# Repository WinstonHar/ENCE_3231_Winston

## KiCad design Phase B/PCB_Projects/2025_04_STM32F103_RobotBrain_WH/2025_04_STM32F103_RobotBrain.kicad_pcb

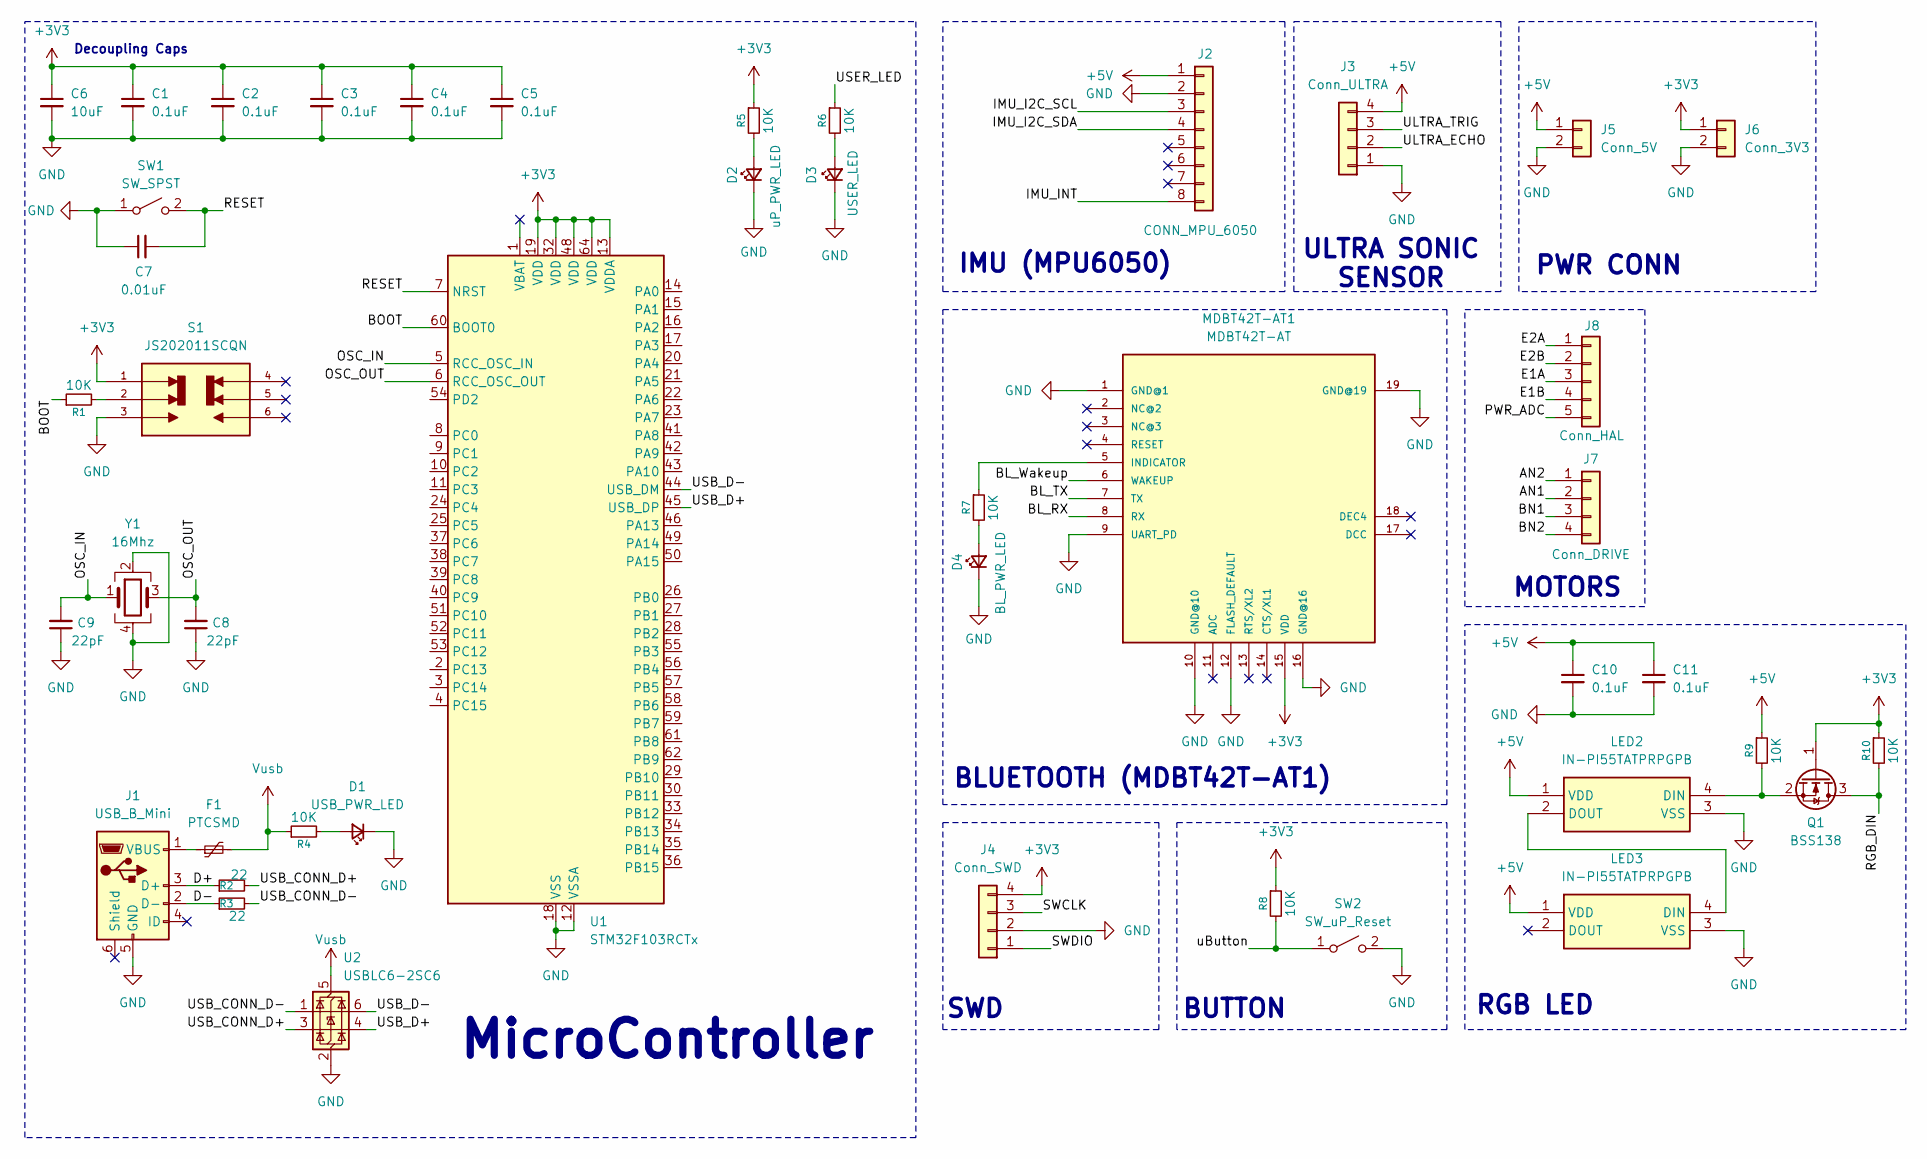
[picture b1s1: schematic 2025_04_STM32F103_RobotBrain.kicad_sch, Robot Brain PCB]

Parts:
C1, C2, C3, C4, C5, C10, C11: 0.1uF; C_0805_2012Metric_Pad1.18x1.45mm_HandSolder; Mfr #P KAM21BR71H104JT
C6: 10uF; C_0805_2012Metric_Pad1.18x1.45mm_HandSolder; Mfr #P LMK212ABJ106KG-T
C7: 0.01uF; C_0805_2012Metric_Pad1.18x1.45mm_HandSolder; Mfr #P KAF21BR72A103JT
C8, C9: 22pF; C_0805_2012Metric_Pad1.18x1.45mm_HandSolder; Mfr #P 0805ZA220JAT2A
D1: USB_PWR_LED; LED_0805_2012Metric_Pad1.15x1.40mm_HandSolder
D2: uP_PWR_LED; LED_0805_2012Metric_Pad1.15x1.40mm_HandSolder
D3: USER_LED; LED_0805_2012Metric_Pad1.15x1.40mm_HandSolder
D4: BL_PWR_LED; LED_0805_2012Metric_Pad1.15x1.40mm_HandSolder
F1: PTCSMD; Fuse_0805_2012Metric_Pad1.15x1.40mm_HandSolder; Mfr #P 0ZCK0050AF2E
J1: USB_B_Mini; USB_Mini-B_Lumberg_2486_01_Horizontal
J2: CONN_MPU_6050; PinSocket_1x08_P2.54mm_Vertical
J3: Conn_ULTRA; PinSocket_1x04_P2.54mm_Vertical
J4: Conn_SWD; PinSocket_1x04_P2.54mm_Vertical
J5: Conn_5V; JST_XH_B2B-XH-A_1x02_P2.50mm_Vertical
J6: Conn_3V3; JST_XH_B2B-XH-A_1x02_P2.50mm_Vertical
J7: Conn_DRIVE; JST_XH_B4B-XH-A_1x04_P2.50mm_Vertical
J8: Conn_HAL; JST_XH_B5B-XH-A_1x05_P2.50mm_Vertical
LED2, LED3: IN-PI55TATPRPGPB; INPI55TATPRPGPB; Manufacturer_Part_Number IN-PI55TATPRPGPB; Mouser Part Number 743-IN-PI55TATPRPGPB
MDBT42T-AT1: MDBT42T-AT; MDBT42T
Q1: BSS138; SOT-23; Mfr #P BSS138
R1, R4, R5, R6, R7, R8, R9, R10: 10K; R_0805_2012Metric_Pad1.20x1.40mm_HandSolder; Mfr #P RK73B2ATTE103J
R2, R3: 22; R_0805_2012Metric_Pad1.20x1.40mm_HandSolder; Mfr #P RC0805FR-7W22RL
S1: JS202011SCQN; SW_JS202011SCQN; PARTREV 26 May 22
SW1: SW_SPST; SW_uP_Reset
SW2: SW_uP_Reset; SW_SPST_PTS647_Sx50
U1: STM32F103RCTx; LQFP-64_10x10mm_P0.5mm; Mfr #P STM32F103RCT6
U2: USBLC6-2SC6; SOT-23-6
Y1: 16Mhz; Crystal_SMD_Abracon_ABM8G-4Pin_3.2x2.5mm; Mfg #p ABM8G-16.000MHZ-18-D2Y-T3

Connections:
+3V3: C1.1, C2.1, C3.1, C4.1, C5.1, C6.1, J4.4, J6.1, MDBT42T-AT1.15 (VDD), Q1.1 (G), R5.1, R8.1, R10.1, S1.1, U1.13 (VDDA), U1.19 (VDD), U1.32 (VDD), U1.48 (VDD), U1.64 (VDD)
+5V: C10.1, C11.1, J2.1, J3.4, J5.1, LED2.1 (VDD), LED3.1 (VDD), R9.1
/AN1: J7.2
/AN2: J7.1
/BL_RX: MDBT42T-AT1.8 (RX)
/BL_TX: MDBT42T-AT1.7 (TX)
/BL_Wakeup: MDBT42T-AT1.6 (WAKEUP)
/BN1: J7.3
/BN2: J7.4
/BOOT: R1.1, U1.60 (BOOT0)
/D+: J1.3 (D+), R2.1
/D-: J1.2 (D-), R3.1
/E1A: J8.3
/E1B: J8.4
/E2A: J8.1
/E2B: J8.2
/IMU_I2C_SCL: J2.3
/IMU_I2C_SDA: J2.4
/IMU_INT: J2.8
/OSC_IN: C9.2, U1.5 (RCC_OSC_IN), Y1.1
/OSC_OUT: C8.2, U1.6 (RCC_OSC_OUT), Y1.3
/PWR_ADC: J8.5
/RESET: C7.2, SW1.2 (B), U1.7 (NRST)
/RGB_DIN: Q1.3 (D), R10.2
/SWCLK: J4.3
/SWDIO: J4.1
/ULTRA_ECHO: J3.2
/ULTRA_TRIG: J3.3
/USB_CONN_D+: R2.2, U2.3 (I/O2)
/USB_CONN_D-: R3.2, U2.1 (I/O1)
/USB_D+: U1.45 (USB_DP), U2.4 (I/O2)
/USB_D-: U1.44 (USB_DM), U2.6 (I/O1)
/USER_LED: R6.1
/uButton: R8.2, SW2.1 (A)
GND: C1.2, C2.2, C3.2, C4.2, C5.2, C6.2, C7.1, C8.1, C9.1, C10.2, C11.2, D1.1 (K), D2.1 (K), D3.1 (K), D4.1 (K), J1.5 (GND), J2.2, J3.1, J4.2, J5.2, J6.2, LED2.3 (VSS), LED3.3 (VSS), MDBT42T-AT1.1 (GND@1), MDBT42T-AT1.9 (UART_PD), MDBT42T-AT1.10 (GND@10), MDBT42T-AT1.12 (FLASH_DEFAULT), MDBT42T-AT1.16 (GND@16), MDBT42T-AT1.19 (GND@19), S1.3, SW1.1 (A), SW2.2 (B), U1.12 (VSSA), U1.18 (VSS), U1.31 (VSS), U1.47 (VSS), U1.63 (VSS), U2.2 (GND), Y1.2, Y1.4
unnamed: D1.2 (A), R4.2
unnamed: D2.2 (A), R5.2
unnamed: D3.2 (A), R6.2
unnamed: D4.2 (A), R7.2
unnamed: F1.1, J1.1 (VBUS)
unnamed: LED2.4 (DIN), Q1.2 (S), R9.2
unnamed: LED2.2 (DOUT), LED3.4 (DIN)
unnamed: MDBT42T-AT1.5 (INDICATOR), R7.1
unnamed: R1.2, S1.2
Vusb: F1.2, R4.1, U2.5 (VBUS)

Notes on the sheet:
BLUETOOTH (MDBT42T-AT1)
ULTRA SONIC SENSOR
RGB LED
PWR CONN
BUTTON
MOTORS
IMU (MPU6050)
MicroController
Decoupling Caps
SWD

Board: 2 copper layers, 42 parts (0 on the bottom side), 25 nets, no tracks yet.

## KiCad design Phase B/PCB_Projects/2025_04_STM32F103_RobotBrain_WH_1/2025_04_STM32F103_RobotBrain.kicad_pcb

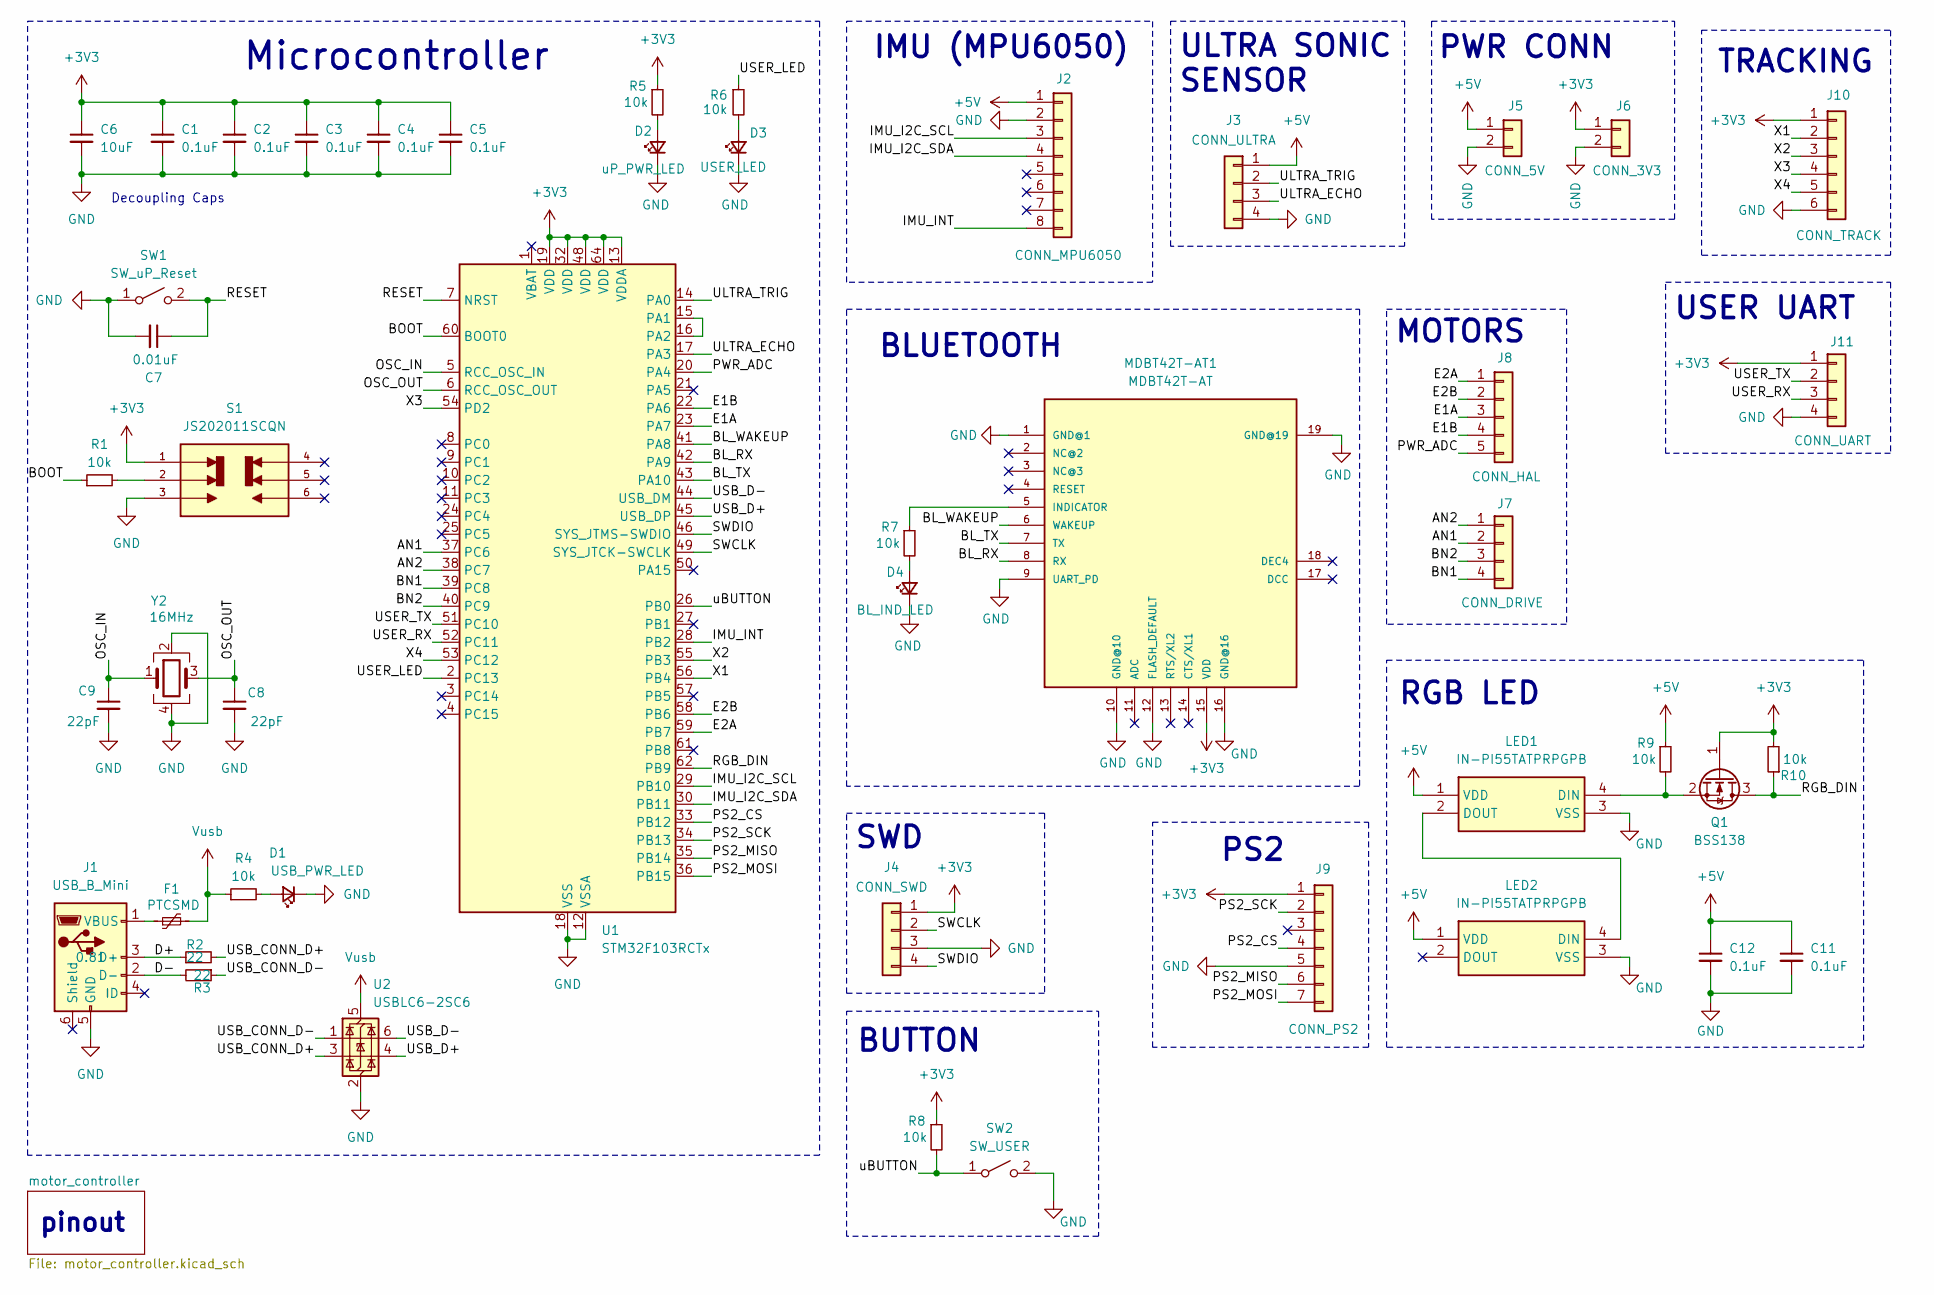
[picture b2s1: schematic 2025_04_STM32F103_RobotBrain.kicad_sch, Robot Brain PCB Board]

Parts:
C1, C2, C3, C4, C5, C11, C12: 0.1uF; C_0805_2012Metric_Pad1.18x1.45mm_HandSolder; Mfr #P KAM21BR71H104JT
C6: 10uF; C_0805_2012Metric_Pad1.18x1.45mm_HandSolder; Mfr #P LMK212ABJ106KG-T
C7: 0.01uF; C_0805_2012Metric_Pad1.18x1.45mm_HandSolder; Mfr #P KAF21BR72A103JT
C8, C9: 22pF; C_0805_2012Metric_Pad1.18x1.45mm_HandSolder; Mfr #P 0805ZA220JAT2A
D1: USB_PWR_LED; LED_0805_2012Metric_Pad1.15x1.40mm_HandSolder; Mfr #P 150080VS75000
D2: uP_PWR_LED; LED_0805_2012Metric_Pad1.15x1.40mm_HandSolder; Mfr #P 150080VS75000
D3: USER_LED; LED_0805_2012Metric_Pad1.15x1.40mm_HandSolder; Mfr #P 150080RS75000
D4: BL_IND_LED; LED_0805_2012Metric_Pad1.15x1.40mm_HandSolder; Mfr #P 150080VS75000
F1: PTCSMD; Fuse_0805_2012Metric_Pad1.15x1.40mm_HandSolder; Mfr #P 0ZCK0050AF2E
J1: USB_B_Mini; USB_Mini-B_Lumberg_2486_01_Horizontal; Mfr #P UJ2-MBH-4-SMT-TR
J2: CONN_MPU6050; PinSocket_1x08_P2.54mm_Vertical
J3: CONN_ULTRA; PinSocket_1x04_P2.54mm_Vertical
J4: CONN_SWD; PinSocket_1x04_P2.54mm_Vertical
J5: CONN_5V; JST_XH_B2B-XH-A_1x02_P2.50mm_Vertical
J6: CONN_3V3; JST_XH_B2B-XH-A_1x02_P2.50mm_Vertical
J7: CONN_DRIVE; JST_XH_B4B-XH-A_1x04_P2.50mm_Vertical
J8: CONN_HAL; JST_XH_B5B-XH-A_1x05_P2.50mm_Vertical
J9: CONN_PS2; PinHeader_1x07_P2.54mm_Vertical
J10: CONN_TRACK; JST_XH_B6B-XH-A_1x06_P2.50mm_Vertical
J11: CONN_UART; JST_XH_B4B-XH-A_1x04_P2.50mm_Vertical
LED1, LED2: IN-PI55TATPRPGPB; INPI55TATPRPGPB; Manufacturer_Part_Number IN-PI55TATPRPGPB; Mouser Part Number 743-IN-PI55TATPRPGPB
MDBT42T-AT1: MDBT42T-AT; MDBT42T
Q1: BSS138; SOT-23; Mfr #P BSS138
R1, R4, R5, R6, R7, R8, R9, R10: 10k; R_0805_2012Metric_Pad1.20x1.40mm_HandSolder; Mfr #P RK73B2ATTE103J
R2, R3: 22; R_0805_2012Metric_Pad1.20x1.40mm_HandSolder; Mfr #P RC0805FR-7W22RL
S1: JS202011SCQN; SW_uP_Boot; PARTREV 26 May 22
SW1: SW_uP_Reset; Mfr #P 434121025816
SW2: SW_USER; SW_SPST_PTS647_Sx50; Mfr #P TL3305BF100QG
U1: STM32F103RCTx; LQFP-64_10x10mm_P0.5mm; Mfr #P STM32F103RCT6
U2: USBLC6-2SC6; SOT-23-6; Mfr #P USBLC6-2SC6
Y2: 16MHz; Crystal_SMD_Abracon_ABM8G-4Pin_3.2x2.5mm; Mfr #P ABM8-16.000MHZ-D1X-T

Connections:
+3V3: C1.1, C2.1, C3.1, C4.1, C5.1, C6.1, J4.1, J6.1, J9.1, J10.1, J11.1, MDBT42T-AT1.15 (VDD), Q1.1 (G), R5.1, R8.1, R10.2, S1.1, U1.13 (VDDA), U1.19 (VDD), U1.32 (VDD), U1.48 (VDD), U1.64 (VDD)
+5V: C11.1, C12.1, J2.1, J3.1, J5.1, LED1.1 (VDD), LED2.1 (VDD), R9.1
/AN1: J7.2, U1.37 (PC6)
/AN2: J7.1, U1.38 (PC7)
/BL_RX: MDBT42T-AT1.8 (RX), U1.42 (PA9)
/BL_TX: MDBT42T-AT1.7 (TX), U1.43 (PA10)
/BL_WAKEUP: MDBT42T-AT1.6 (WAKEUP), U1.41 (PA8)
/BN1: J7.4, U1.39 (PC8)
/BN2: J7.3, U1.40 (PC9)
/BOOT: R1.1, U1.60 (BOOT0)
/D+: J1.3 (D+), R2.1
/D-: J1.2 (D-), R3.2
/E1A: J8.3, U1.23 (PA7)
/E1B: J8.4, U1.22 (PA6)
/E2A: J8.1, U1.59 (PB7)
/E2B: J8.2, U1.58 (PB6)
/IMU_I2C_SCL: J2.3, U1.29 (PB10)
/IMU_I2C_SDA: J2.4, U1.30 (PB11)
/IMU_INT: J2.8, U1.28 (PB2)
/OSC_IN: C9.1, U1.5 (RCC_OSC_IN), Y2.1
/OSC_OUT: C8.1, U1.6 (RCC_OSC_OUT), Y2.3
/PS2_CS: J9.4, U1.33 (PB12)
/PS2_MISO: J9.6, U1.35 (PB14)
/PS2_MOSI: J9.7, U1.36 (PB15)
/PS2_SCK: J9.2, U1.34 (PB13)
/PWR_ADC: J8.5, U1.20 (PA4)
/RESET: C7.1, SW1.2 (B), U1.7 (NRST)
/RGB_DIN: Q1.3 (D), R10.1, U1.62 (PB9)
/SWCLK: J4.2, U1.49 (SYS_JTCK-SWCLK)
/SWDIO: J4.4, U1.46 (SYS_JTMS-SWDIO)
/ULTRA_ECHO: J3.3, U1.17 (PA3)
/ULTRA_TRIG: J3.2, U1.14 (PA0)
/USB_CONN_D+: R2.2, U2.3 (I/O2)
/USB_CONN_D-: R3.1, U2.1 (I/O1)
/USB_D+: U1.45 (USB_DP), U2.4 (I/O2)
/USB_D-: U1.44 (USB_DM), U2.6 (I/O1)
/USER_LED: R6.1, U1.2 (PC13)
/USER_RX: J11.3, U1.52 (PC11)
/USER_TX: J11.2, U1.51 (PC10)
/X1: J10.2, U1.56 (PB4)
/X2: J10.3, U1.55 (PB3)
/X3: J10.4, U1.54 (PD2)
/X4: J10.5, U1.53 (PC12)
/uBUTTON: R8.2, SW2.1 (A), U1.26 (PB0)
GND: C1.2, C2.2, C3.2, C4.2, C5.2, C6.2, C7.2, C8.2, C9.2, C11.2, C12.2, D1.1 (K), D2.1 (K), D3.1 (K), D4.1 (K), J1.5 (GND), J2.2, J3.4, J4.3, J5.2, J6.2, J9.5, J10.6, J11.4, LED1.3 (VSS), LED2.3 (VSS), MDBT42T-AT1.1 (GND@1), MDBT42T-AT1.9 (UART_PD), MDBT42T-AT1.10 (GND@10), MDBT42T-AT1.12 (FLASH_DEFAULT), MDBT42T-AT1.16 (GND@16), MDBT42T-AT1.19 (GND@19), S1.3, SW1.1 (A), SW2.2 (B), U1.12 (VSSA), U1.18 (VSS), U1.31 (VSS), U1.47 (VSS), U1.63 (VSS), U2.2 (GND), Y2.2, Y2.4
unnamed: D1.2 (A), R4.2
unnamed: D2.2 (A), R5.2
unnamed: D3.2 (A), R6.2
unnamed: D4.2 (A), R7.2
unnamed: F1.1, J1.1 (VBUS)
unnamed: LED1.4 (DIN), Q1.2 (S), R9.2
unnamed: LED1.2 (DOUT), LED2.4 (DIN)
unnamed: MDBT42T-AT1.5 (INDICATOR), R7.1
unnamed: R1.2, S1.2
unnamed: U1.15 (PA1), U1.16 (PA2)
Vusb: F1.2, R4.1, U2.5 (VBUS)

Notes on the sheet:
PWR CONN
ULTRA SONIC SENSOR
Decoupling Caps
BUTTON
MOTORS
PS2
RGB LED
Microcontroller
TRACKING
pinout
IMU (MPU6050)
SWD
USER UART
BLUETOOTH

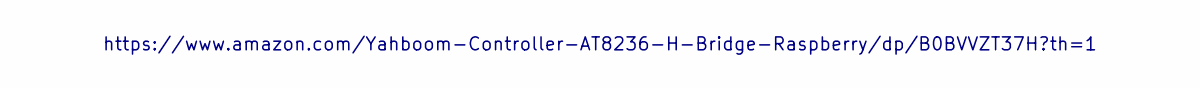
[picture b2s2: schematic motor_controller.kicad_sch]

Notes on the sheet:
https://www.amazon.com/Yahboom-Controller-AT8236-H-Bridge-Raspberry/dp/B0BVVZT37H?th=1

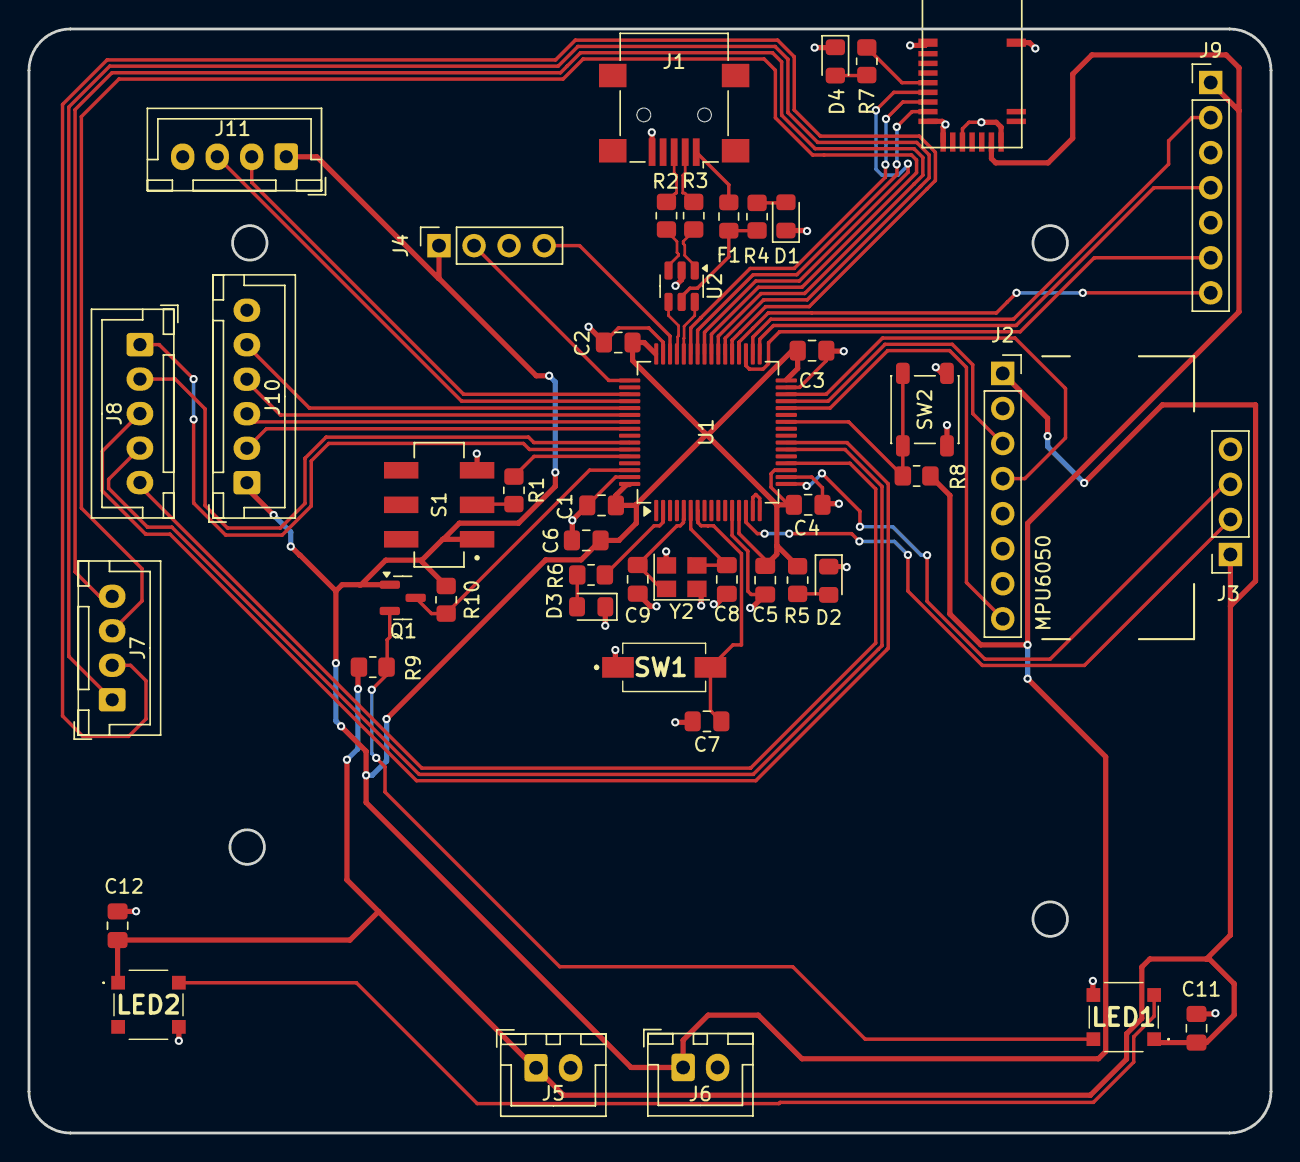
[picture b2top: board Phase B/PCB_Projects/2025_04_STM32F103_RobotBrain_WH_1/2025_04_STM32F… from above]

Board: 2 copper layers, 90.0 x 80.0 mm, 47 parts (0 on the bottom side), 56 nets.

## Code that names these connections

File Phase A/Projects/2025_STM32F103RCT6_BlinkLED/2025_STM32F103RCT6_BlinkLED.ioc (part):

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Mcu.Name=STM32F103R(C-D-E)Tx
Mcu.Package=LQFP64
Mcu.UserName=STM32F103RCTx
PA10.Mode=Asynchronous
PA10.Signal=USART1_RX
PA11.Mode=Device
PA11.Signal=USB_DM
PA12.Mode=Device
PA12.Signal=USB_DP
PA13.Mode=Serial_Wire
PA13.Signal=SYS_JTMS-SWDIO
PA14.Mode=Serial_Wire
PA14.Signal=SYS_JTCK-SWCLK
PA4.GPIOParameters=GPIO_Label
PA4.GPIO_Label=PWR_ADC
PA4.Signal=ADCx_IN4
PA7.GPIOParameters=GPIO_Label
PA7.GPIO_Label=RGB_DIN
PA7.Signal=GPIO_Output
PA8.GPIOParameters=GPIO_Label
PA8.GPIO_Label=BL_WAKEUP
PA8.Signal=GPIO_Output
PA9.Mode=Asynchronous
PA9.Signal=USART1_TX
PB0.GPIOParameters=GPIO_Label
PB0.GPIO_Label=uBUTTON
PB0.Signal=GPIO_Input
PB5.GPIOParameters=GPIO_Label
PB5.GPIO_Label=IMU_INT
PB5.Signal=GPIO_Input
PB6.Mode=I2C
PB6.Signal=I2C1_SCL
PB7.Mode=I2C
PB7.Signal=I2C1_SDA
PC13-TAMPER-RTC.GPIOParameters=GPIO_Label
PC13-TAMPER-RTC.GPIO_Label=USER_LED
PC13-TAMPER-RTC.Signal=GPIO_Output
PD0-OSC_IN.Mode=HSE-External-Oscillator
PD0-OSC_IN.Signal=RCC_OSC_IN
PD1-OSC_OUT.Mode=HSE-External-Oscillator
PD1-OSC_OUT.Signal=RCC_OSC_OUT
board=custom

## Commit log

2025-04-20 Uploading initial files to git
2025-05-06 Robot Brain project, reformat repo
2025-05-20 Added Phase C, Completed Battery Monitor Assignment, Restructuring
2025-05-20 adding block diagram
